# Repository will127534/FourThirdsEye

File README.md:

# FourThirdsEye: Opensource Micro Four Thirds camera module based on IMX294

## Introduction
Welcome to the **FourThirdsEye** project, an open-source camera board designed for Raspberry Pi 5 and Raspberry Pi Compute Module 4 boards using a Micro Four Thirds format image sensor IMX294. This project aims to provide a high-quality and accessible camera module for advanced Raspberry Pi projects. The board is designed using KiCad v8.

FourThirdsEye captures 10.7 Mpix images and 4K (4096 x 2160) videos with improved low-light performance and dynamic range (4.63 um pixel size). It's perfect for photography enthusiasts, developers, and makers who want to level up their Raspberry Pi projects with a powerful camera.

Also see [Quick Start Guide](https://github.com/will127534/FourThirdsEye/wiki/FourThirdsEye-Quick-Start-Guide)

## Features
* **Open-source hardware and software**
* IMX294 sensor
* Integrated TMP117 temperature sensor
* Integrated ICM-42688-P 6-axis IMU with FSYNC connected to sensor's VSYNC
* Compatible with Raspberry Pi5 and Raspberry Pi Compute Module 4 boards with a 22-pin FPC connector and 4-lane MIPI-CSI (same pinout as Raspberry Pi Compute Module 4 IO Board)

## Notes
* Gerber, BOM and CPL file for JLCPCB is under [/Gerber](/Gerber)
* [Interactive BOM](https://htmlpreview.github.io/?https://github.com/will127534/FourThirdsEye/blob/main/ibom.html) [(provided by InteractiveHtmlBom)
](https://github.com/openscopeproject/InteractiveHtmlBom)
* Driver for Raspberry Pi: [https://github.com/will127534/imx294-v4l2-driver](https://github.com/will127534/imx294-v4l2-driver)
* 3D model for the board and sensor, C-mount adaptor and E-mount adaptor + Filter design is under [/3D_model](/3D_model), note that you will need to grab the metal ring from a E-mount (lens extender or replacements parts) and mount it to the 3D printed adaptor, for C-mount adaptor it is designed for CNC machine.
* Limited amount on [https://shop.willwhang.dev/](https://shop.willwhang.dev/)  for sell

## Sidenotes
IMX294 with CSI-2 interface mode is running at 1.78Gbps, technically breaking the spec for RPI5 (1.5Gbps) and CM4 (1Gbps?...they didn't really state it clearly) but I have tested on both platforms and are both working properly. But the one catch is that FPC cable quality/length will impact the data transmition, I've see black/bad pixel data scattering in the frames with a long 50cm cable, but it is fine with the 20cm cable. Also to actually utilized the full capacity/FPS of the sensor on RPI5, you will need to [overclock](https://www.willwhang.dev/Solar-eclipse-2024/#overclocking-the-rp1-for-enhanced-pisp-performance) RP1 (Camera Frontend) so it can handle the sensor at 60 FPS 4K. The sensor itself is also quite interesting because it is actually a quad bayer array just with subpixel combined output only, it is technically capable of sending high/low gain frame output but I'm still waiting for the HDR support on RPI5 to actually test it.

As for the PCB board design, the goal is to make a miniaturized camera board, but because of that I have to use smaller via sizes (0.2mm) and via-in-pad for the decoupling capacitors. There is also a bunch of tiny common mode CSI-2 filter that it might be hard for hand soldering so PCBA services or stencil + paste is the perfer way to build it.

Last thing is that if you are looking to capture RAW videos with Raspberry Pi 5, checkout [CinePi](https://github.com/cinepi/cinepi-sdk) from [@schoolpost](https://csabanagy.ca).

## Support
For questions, issues, or suggestions, please open an issue in the [GitHub repository](https://github.com/will127534/FourThirdsEye/issues)

## Schematic

## PCB

*Screw hole sizes are M3

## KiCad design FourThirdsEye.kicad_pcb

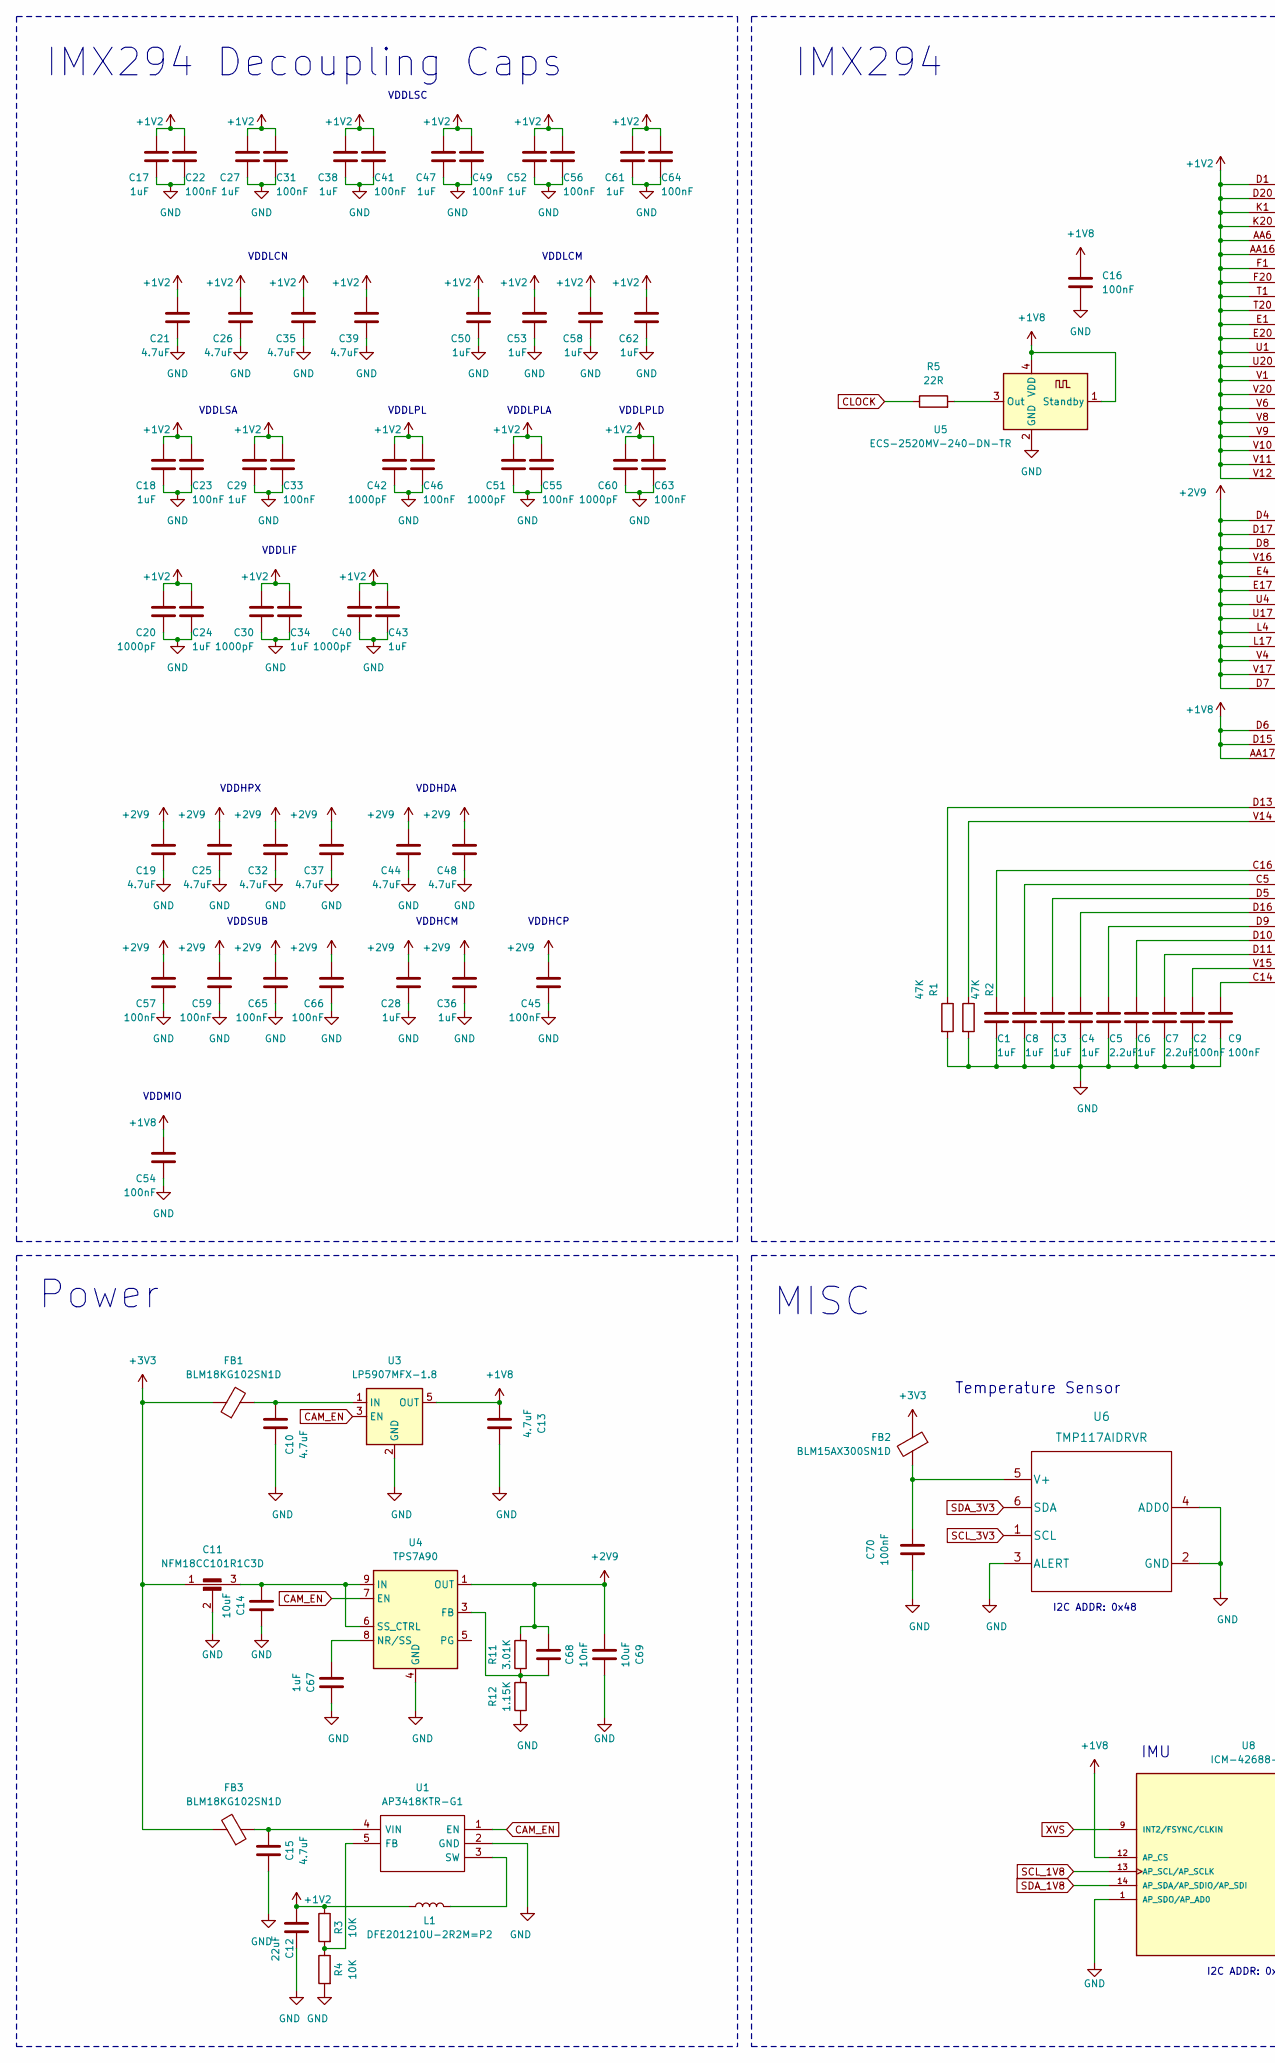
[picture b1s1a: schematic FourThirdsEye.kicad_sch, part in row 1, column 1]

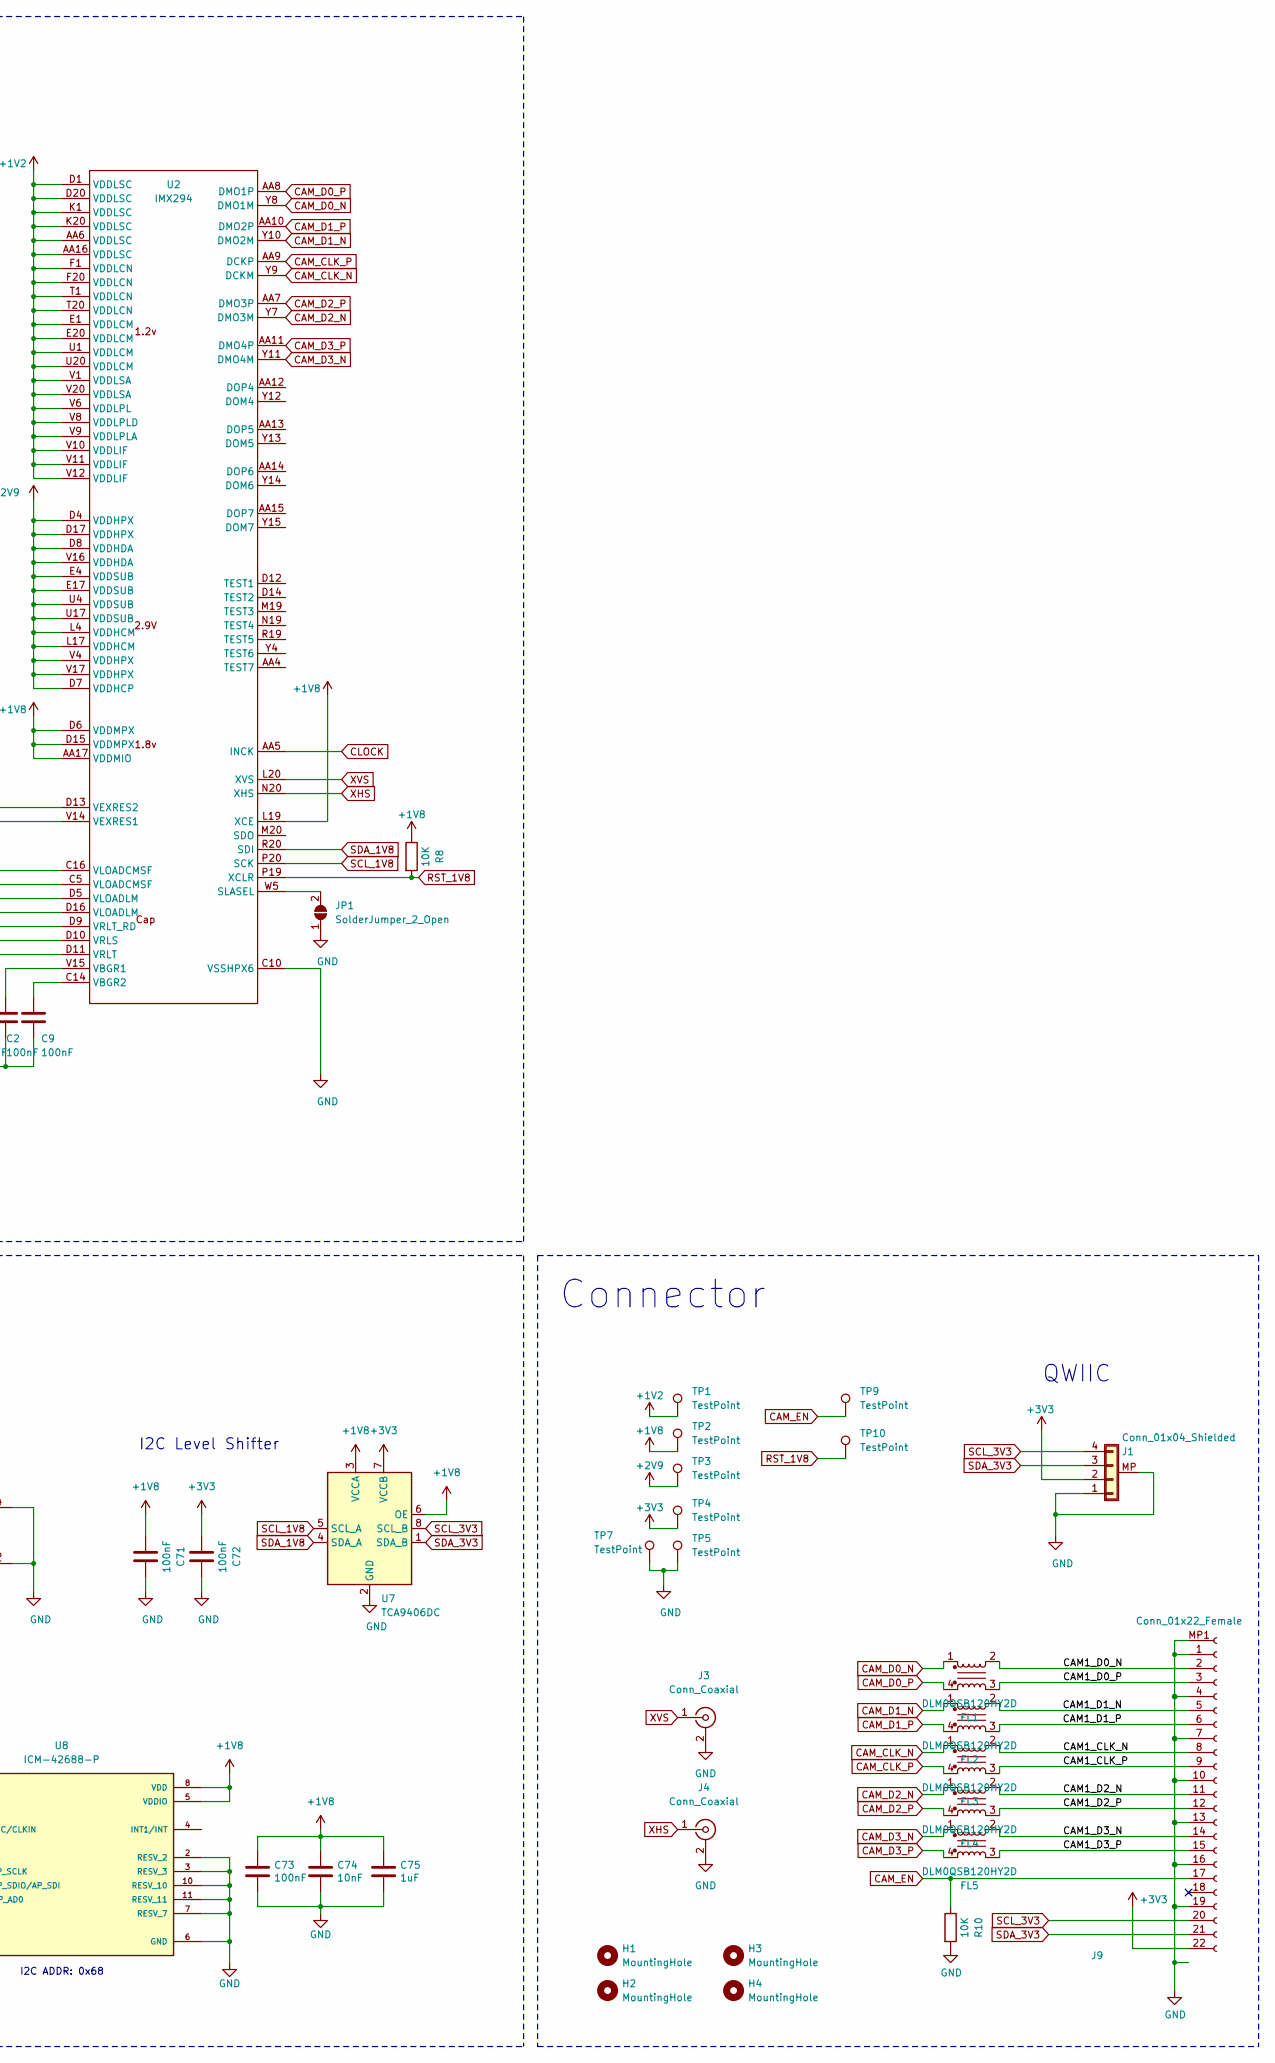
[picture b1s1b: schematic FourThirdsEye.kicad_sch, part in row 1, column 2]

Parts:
C1, C3, C4, C6, C8, C17, C18, C24, C27, C28, C29, C34, C36, C38, C43, C47, C50, C52, C53, C58, C61, C62, C67, C75: 1uF; C_0402_1005Metric
C2, C9, C16, C22, C23, C31, C33, C41, C45, C46, C49, C54, C55, C56, C57, C59, C63, C64, C65, C66, C70, C71, C72, C73: 100nF; C_0402_1005Metric
C5, C7: 2.2uF; C_0603_1608Metric
C10, C13, C15, C19, C21, C25, C26, C32, C35, C37, C39, C44, C48: 4.7uF; C_0603_1608Metric
C11: NFM18CC101R1C3D
C12: 22uF; C_0603_1608Metric
C14, C69: 10uF; C_0603_1608Metric
C20, C30, C40, C42, C51, C60: 1000pF; C_0402_1005Metric
C68, C74: 10nF; C_0402_1005Metric
FB1, FB3: BLM18KG102SN1D; L_0603_1608Metric
FB2: BLM15AX300SN1D; L_0402_1005Metric
FL1, FL2, FL3, FL4, FL5: DLM0QSB120HY2D
H1, H2, H3, H4: MountingHole; MountingHole_3.2mm_M3
J1: Conn_01x04_Shielded; JST_SH_BM04B-SRSS-TB_1x04-1MP_P1.00mm_Vertical
J3, J4: Conn_Coaxial; U.FL_Hirose_U.FL-R-SMT-1_Vertical
J9: Conn_01x22_Female; TF3822S05SV830; Part Description 22 Position FFC, FPC Connector Contacts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
JP1: SolderJumper_2_Open; SolderJumper-2_P1.3mm_Open_RoundedPad1.0x1.5mm
L1: DFE201210U-2R2M=P2; L_0805_2012Metric
R1, R2: 47K; R_0402_1005Metric
R3, R4, R8, R10: 10K; R_0402_1005Metric
R5: 22R; R_0402_1005Metric
R11: 3.01K; R_0402_1005Metric
R12: 1.15K; R_0402_1005Metric
TP1, TP2, TP3, TP4, TP5, TP7, TP9, TP10: TestPoint; TestPoint_Pad_D1.0mm
U1: AP3418KTR-G1; SOT-23-5; Mouser Part Number 621-AP3418KTR-G1
U2: IMX294
U3: LP5907MFX-1.8; SOT-23-5
U4: TPS7A90; Texas_S-PDSO-N10_EP1.2x2mm
U5: ECS-2520MV-240-DN-TR; Oscillator_SMD_Abracon_ASDMB-4Pin_2.5x2.0mm
U6: TMP117AIDRVR
U7: TCA9406DC; TCA9406DCUR
U8: ICM-42688-P; PQFN50P300X250X97-14N; PARTREV 1.2

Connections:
+1V2: C12.2, C17.2, C18.2, C20.2, C21.2, C22.1, C23.1, C24.1, C26.2, C27.2, C29.2, C30.2, C31.1, C33.1, C34.1, C35.2, C38.2, C39.2, C40.2, C41.1, C42.2, C43.1, C46.1, C47.2, C49.1, C50.2, C51.2, C52.2, C53.2, C55.1, C56.1, C58.2, C60.2, C61.2, C62.2, C63.1, C64.1, L1.2, R3.1, TP1.1, U2.AA6 (VDDLSC), U2.AA16 (VDDLSC), U2.D1 (VDDLSC), U2.D20 (VDDLSC), U2.E1 (VDDLCM), U2.E20 (VDDLCM), U2.F1 (VDDLCN), U2.F20 (VDDLCN), U2.K1 (VDDLSC), U2.K20 (VDDLSC), U2.T1 (VDDLCN), U2.T20 (VDDLCN), U2.U1 (VDDLCM), U2.U20 (VDDLCM), U2.V1 (VDDLSA), U2.V6 (VDDLPL), U2.V8 (VDDLPLD), U2.V9 (VDDLPLA), U2.V10 (VDDLIF), U2.V11 (VDDLIF), U2.V12 (VDDLIF), U2.V20 (VDDLSA)
+1V8: C13.1, C16.1, C54.2, C71.1, C73.1, C74.1, C75.1, R8.1, TP2.1, U2.AA17 (VDDMIO), U2.D6 (VDDMPX), U2.D15 (VDDMPX), U2.L19 (XCE), U3.5 (OUT), U5.1 (Standby), U5.4 (VDD), U7.3 (VCCA), U7.6 (OE), U8.5 (VDDIO), U8.8 (VDD), U8.12 (AP_CS)
+2V9: C19.2, C25.2, C28.2, C32.2, C36.2, C37.2, C44.2, C45.2, C48.2, C57.2, C59.2, C65.2, C66.2, C68.2, C69.1, R11.2, TP3.1, U2.D4 (VDDHPX), U2.D7 (VDDHCP), U2.D8 (VDDHDA), U2.D17 (VDDHPX), U2.E4 (VDDSUB), U2.E17 (VDDSUB), U2.L4 (VDDHCM), U2.L17 (VDDHCM), U2.U4 (VDDSUB), U2.U17 (VDDSUB), U2.V4 (VDDHPX), U2.V16 (VDDHDA), U2.V17 (VDDHPX), U4.1 (OUT), U4.2 (OUT)
+3V3: C11.1, C72.1, FB1.1, FB2.1, FB3.2, J1.2, J9.22, TP4.1, U7.7 (VCCB)
/CAM1_CLK_N: FL3.2, J9.8
/CAM1_CLK_P: FL3.3, J9.9
/CAM1_D0_N: FL1.2, J9.2
/CAM1_D0_P: FL1.3, J9.3
/CAM1_D1_N: FL2.2, J9.5
/CAM1_D1_P: FL2.3, J9.6
/CAM1_D2_N: FL4.2, J9.11
/CAM1_D2_P: FL4.3, J9.12
/CAM1_D3_N: FL5.2, J9.14
/CAM1_D3_P: FL5.3, J9.15
CAM_CLK_N: FL3.1, U2.Y9 (DCKM)
CAM_CLK_P: FL3.4, U2.AA9 (DCKP)
CAM_D0_N: FL1.1, U2.Y8 (DMO1M)
CAM_D0_P: FL1.4, U2.AA8 (DMO1P)
CAM_D1_N: FL2.1, U2.Y10 (DMO2M)
CAM_D1_P: FL2.4, U2.AA10 (DMO2P)
CAM_D2_N: FL4.1, U2.Y7 (DMO3M)
CAM_D2_P: FL4.4, U2.AA7 (DMO3P)
CAM_D3_N: FL5.1, U2.Y11 (DMO4M)
CAM_D3_P: FL5.4, U2.AA11 (DMO4P)
CAM_EN: J9.17, R10.1, TP9.1, U1.1 (EN), U3.3 (EN), U4.7 (EN)
CLOCK: R5.1, U2.AA5 (INCK)
GND: C1.2, C2.2, C3.2, C4.2, C5.2, C6.2, C7.2, C8.2, C9.2, C10.1, C11.2, C12.1, C13.2, C14.2, C15.2, C16.2, C17.1, C18.1, C19.1, C20.1, C21.1, C22.2, C23.2, C24.2, C25.1, C26.1, C27.1, C28.1, C29.1, C30.1, C31.2, C32.1, C33.2, C34.2, C35.1, C36.1, C37.1, C38.1, C39.1, C40.1, C41.2, C42.1, C43.2, C44.1, C45.1, C46.2, C47.1, C48.1, C49.2, C50.1, C51.1, C52.1, C53.1, C54.1, C55.2, C56.2, C57.1, C58.1, C59.1, C60.1, C61.1, C62.1, C63.2, C64.2, C65.1, C66.1, C67.2, C69.2, C70.1, C71.2, C72.2, C73.2, C74.2, C75.2, J1.1, J1.MP (Shield), J3.2 (Ext), J4.2 (Ext), J9.1, J9.4, J9.7, J9.10, J9.13, J9.16, J9.19, J9.MP1 (Pin_MP), J9.MP2 (Pin_MP), J9.MP3 (Pin_MP), J9.MP4 (Pin_MP), JP1.1 (A), R1.2, R2.2, R4.2, R10.2, R12.1, TP5.1, TP7.1, U1.2 (GND), U2.C4 (VSSHPX1), U2.C6 (VSSHPX2), U2.C7 (VSSHCP3), U2.C8 (VSSHDA4), U2.C9 (VSSHPX5), U2.C10 (VSSHPX6), U2.C11 (VSSHPX7), U2.C12 (VSSHPX8), U2.C15 (VSSHPX9), U2.C17 (VSSHPX10), U2.D2 (VSSLSC11), U2.D19 (VSSLSC12), U2.E2 (VSSLCM13), U2.E19 (VSSLCM14), U2.F2 (VSSLCN15), U2.F19 (VSSLCN16), U2.K2 (VSSLSC17), U2.K19 (VSSLSC18), U2.L3 (VSSHCM19), U2.L18 (VSSHCM20), U2.T2 (VSSLCN21), U2.T19 (VSSLCN22), U2.U2 (VSSLCM23), U2.U19 (VSSLCM24), U2.V2 (VSSLSA25), U2.V19 (VSSLSA26), U2.W4 (VSSHPX27), U2.W6 (VSSLPL28), U2.W8 (VSSLPLD29), U2.W9 (VSSLPLA30), U2.W10 (VSSLIF31), U2.W11 (VSSLIF32), U2.W12 (VSSLIF33), U2.W16 (VSSHDA34), U2.W17 (VSSHPX35), U2.Y5 (VSSLPLD36), U2.Y6 (VSSLSC37), U2.Y16 (VSSLSC38), U3.2 (GND), U4.4 (GND), U4.11 (GND), U5.2 (GND), U6.2 (GND), U6.3 (ALERT), U6.4 (ADD0), U7.2 (GND), U8.1 (AP_SDO/AP_AD0), U8.2 (RESV_2), U8.3 (RESV_3), U8.6 (GND), U8.7 (RESV_7), U8.10 (RESV_10), U8.11 (RESV_11)
unnamed: C1.1, U2.C16 (VLOADCMSF)
unnamed: C3.1, U2.D5 (VLOADLM)
unnamed: C4.1, U2.D16 (VLOADLM)
unnamed: C8.1, U2.C5 (VLOADCMSF)
unnamed: JP1.2 (B), U2.W5 (SLASEL)
unnamed: R3.2, R4.1, U1.5 (FB)
unnamed: L1.1, U1.3 (SW)
unnamed: C15.1, FB3.1, U1.4 (VIN)
unnamed: C2.1, U2.V15 (VBGR1)
unnamed: C9.1, U2.C14 (VBGR2)
unnamed: R2.1, U2.V14 (VEXRES1)
unnamed: R1.1, U2.D13 (VEXRES2)
unnamed: C6.1, U2.D10 (VRLS)
unnamed: C7.1, U2.D11 (VRLT)
unnamed: C5.1, U2.D9 (VRLT_RD)
unnamed: C10.2, FB1.2, U3.1 (IN)
unnamed: C68.1, R11.1, R12.2, U4.3 (FB)
unnamed: C67.1, U4.8 (NR/SS)
unnamed: C11.3, C14.1, U4.6 (SS_CTRL), U4.9 (IN), U4.10 (IN)
unnamed: R5.2, U5.3 (Out)
unnamed: C70.2, FB2.2, U6.5 (V+)
RST_1V8: R8.2, TP10.1, U2.P19 (XCLR)
SCL_1V8: U2.P20 (SCK), U7.5 (SCL_A), U8.13 (AP_SCL/AP_SCLK)
SCL_3V3: J1.4, J9.20, U6.1 (SCL), U7.8 (SCL_B)
SDA_1V8: U2.R20 (SDI), U7.4 (SDA_A), U8.14 (AP_SDA/AP_SDIO/AP_SDI)
SDA_3V3: J1.3, J9.21, U6.6 (SDA), U7.1 (SDA_B)
XHS: J4.1 (In), U2.N20 (XHS)
XVS: J3.1 (In), U2.L20 (XVS), U8.9 (INT2/FSYNC/CLKIN)

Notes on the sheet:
Temperature Sensor
VDDLPL
VDDLCM
VDDLCN
I2C Level Shifter
VDDHPX
VDDMIO
VDDHCM
Power
I2C ADDR: 0x68
VDDHDA
VDDHCP
I2C ADDR: 0x48
VDDLSA
Connector
VDDLSC
MISC
VDDLIF
IMX294
VDDLPLD
IMU
IMX294 Decoupling Caps
VDDSUB
QWIIC
VDDLPLA

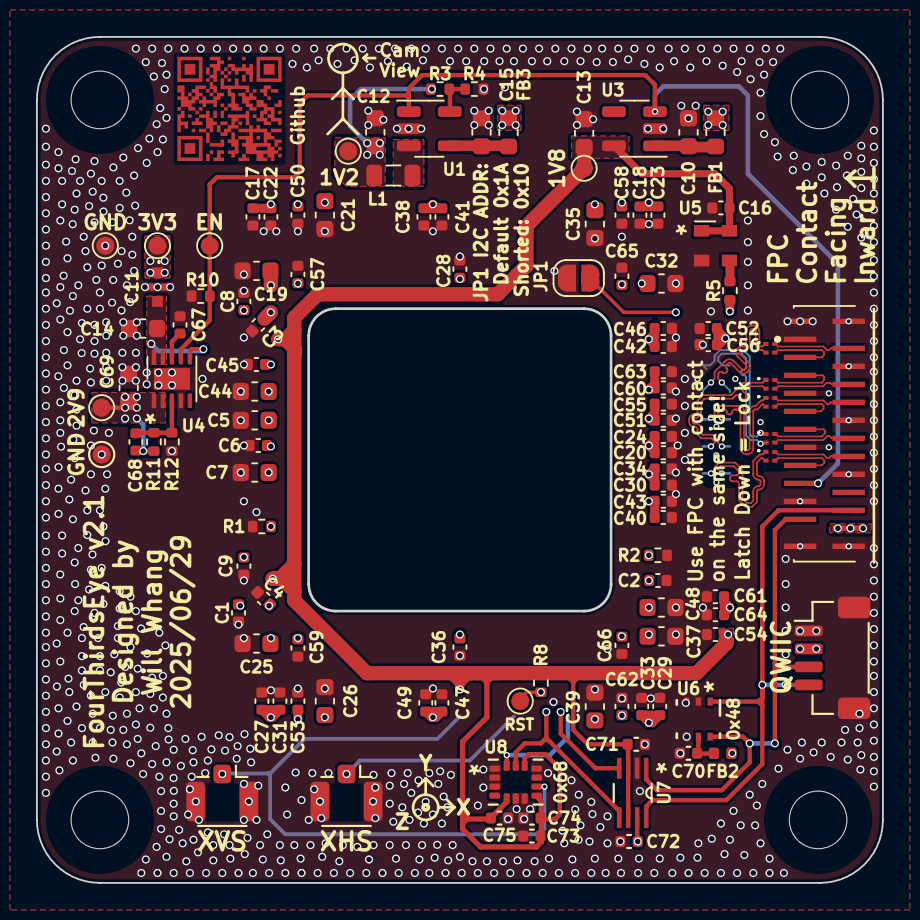
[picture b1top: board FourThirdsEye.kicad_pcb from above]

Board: 4 copper layers, 47.0 x 47.0 mm, 118 parts (1 on the bottom side), 55 nets.

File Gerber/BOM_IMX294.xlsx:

Comment | Designator | Footprint | JLCPCB Part #（optional）
1uF | C1,C36,C53,C4,C18,C6,C17,C75,C43,C62,C24,C28,C38,C61,C52,C50,C47,C67,C3,C8,C27,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 | C_0402_1005Metric | C115046
C_Feedthrough | C11 | NFM18CC101R1C3D | C111493
22uF | C12 | C_0603_1608Metric | C59461
4.7uF | C32,C37,C44,C21,C13,C35,C10,C25,C39,C26,C19,C48,C15 | C_0603_1608Metric | C389010
2.2uF | C5,C7 | C_0603_1608Metric | C513691
1000pF | C60,C42,C20,C30,C51,C40 | C_0402_1005Metric | C338101
10nF | C68,C74 | C_0402_1005Metric | C15195
10uF | C69,C14 | C_0603_1608Metric | C2959727
100nF | C70,C41,C55,C45,C66,C46,C49,C31,C2,C22,C54,C59,C73,C56,C65,C64,C9,C71,C33,C57,C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 | C_0402_1005Metric | C1525
BLM15AX300SN1D | FB2 | L_0402_1005Metric | C71813
BLM18KG102SN1D | FB3,FB1 | L_0603_1608Metric | C160982
DLM0QSB120HY2D | FL4,FL2,FL1,FL3,FL5 | DLM0QSB120HY2D | C3211477
QWIIC_CONNECTORJS-1MM | J1 | JST_SH_BM04B-SRSS-TB_1x04-1MP_P1.00mm_Vertical | C160390
Conn_Coaxial | J4,J3 | U.FL_Hirose_U.FL-R-SMT-1_Vertical | C5137195
Conn_01x22_Female | J9 | TF3822S05SV830 | C6552695
DFE201210U-2R2M=P2 | L1 | L_0805_2012Metric | C2049745
47K | R1,R2 | R_0402_1005Metric | C25792
10K | R10,R3,R4,R8 | R_0402_1005Metric | C25744
3.01K | R11 | R_0402_1005Metric | C304603
1.15K | R12 | R_0402_1005Metric | C477191
22R | R5 | R_0402_1005Metric | C413049
AP3418KTR-G1 | U1 | SOT-23-5 | C500769
LP5907MFX-1.8 | U3 | SOT-23-5 | C92498
TPS7A9001DSKR | U4 | Texas_S-PDSO-N10_EP1.2x2mm | C840111
ECS-2520MV-240-DN-TR | U5 | Oscillator_SMD_Abracon_ASDMB-4Pin_2.5x2.0mm | C5375391
TMP117AIDRVR | U6 | TMP117AIDRVR | C699536
TCA9406DC | U7 | TCA9406DCUR | C840107
ICM-42688-P | U8 | PQFN50P300X250X97-14N | C1850418

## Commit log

2024-06-14 Init
2024-06-14 Adding images
2025-11-24 Uploading 3D model for the v2.1 board
    Let's see how Github renders this STL.....
2025-11-24 upload V2.1 files and Cmount adaptor 3D model
2025-11-24 Update README with new images and details
    Updated images and descriptions in the README.
2025-11-24 adding sch jpeg
2025-11-24 Revise README for FourThirdsEye project
    Updated project details and specifications in README.
2026-06-28 Update shop link for limited product availability
